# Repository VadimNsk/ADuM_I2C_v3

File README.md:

# ADuM_I2C_v3
Преобразование уровней шины I2C и двух сигналов

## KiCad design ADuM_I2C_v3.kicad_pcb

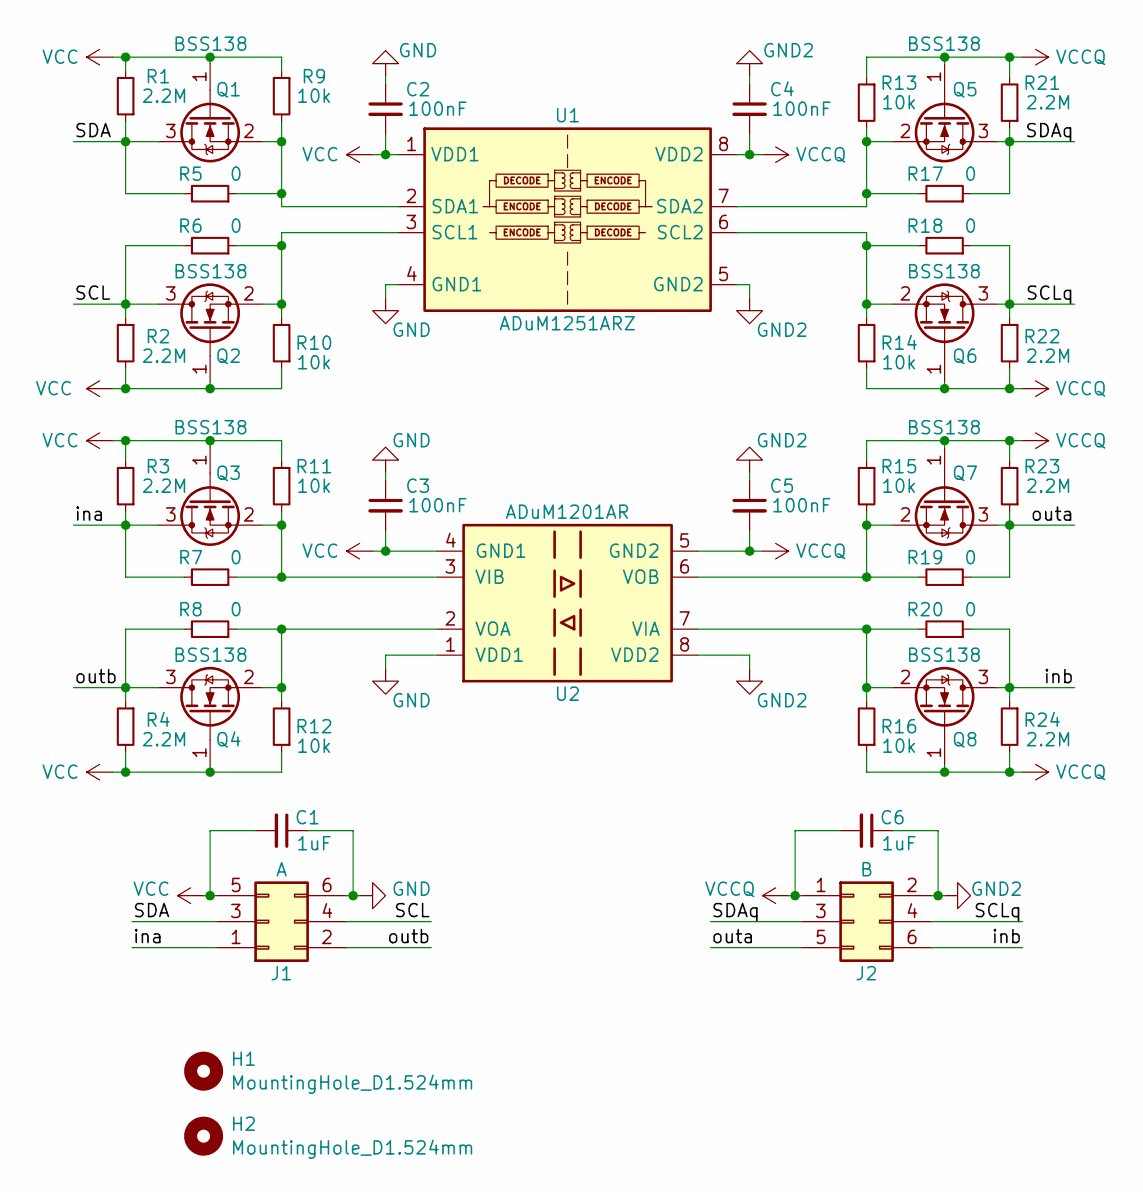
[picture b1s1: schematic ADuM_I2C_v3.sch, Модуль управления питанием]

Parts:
C1, C6: 1uF; C_0603_1608Metric
C2, C3, C4, C5: 100nF; C_0603_1608Metric
H1, H2: MountingHole_D1.524mm
J1: A; PinHeader_2x03_P1.27mm_Horizontal_short
J2: B; PinHeader_2x03_P1.27mm_Horizontal_short
Q1, Q2, Q3, Q4, Q5, Q6, Q7, Q8: BSS138; SOT-23
R1, R2, R3, R4, R21, R22, R23, R24: 2.2M; R_0603_1608Metric
R5, R6, R7, R8, R17, R18, R19, R20: 0; R_0603_1608Metric
R9, R10, R11, R12, R13, R14, R15, R16: 10k; R_0603_1608Metric
U1: ADuM1251ARZ; SOIC-8_3.9x4.9mm_P1.27mm
U2: ADuM1201AR; SOIC-8_3.9x4.9mm_P1.27mm

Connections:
/SCL: J1.4, Q2.3 (D), R2.1, R6.2
/SCLq: J2.4, Q6.3 (D), R18.1, R22.1
/SDA: J1.3, Q1.3 (D), R1.1, R5.2
/SDAq: J2.3, Q5.3 (D), R17.1, R21.1
/ina: J1.1, Q3.3 (D), R3.1, R7.2
/inb: J2.6, Q8.3 (D), R20.1, R24.1
/outa: J2.5, Q7.3 (D), R19.1, R23.1
/outb: J1.2, Q4.3 (D), R4.1, R8.2
GND: C1.1, C2.1, C3.1, J1.6, U1.4 (GND1), U2.1 (VDD1)
GND2: C4.1, C5.1, C6.1, J2.2, U1.5 (GND2), U2.8 (VDD2)
unnamed: Q1.2 (S), R5.1, R9.2, U1.2 (SDA1)
unnamed: Q2.2 (S), R6.1, R10.2, U1.3 (SCL1)
unnamed: Q3.2 (S), R7.1, R11.2, U2.3 (VIB)
unnamed: Q4.2 (S), R8.1, R12.2, U2.2 (VOA)
unnamed: Q5.2 (S), R13.2, R17.2, U1.7 (SDA2)
unnamed: Q6.2 (S), R14.2, R18.2, U1.6 (SCL2)
unnamed: Q7.2 (S), R15.2, R19.2, U2.6 (VOB)
unnamed: Q8.2 (S), R16.2, R20.2, U2.7 (VIA)
VCC: C1.2, C2.2, C3.2, J1.5, Q1.1 (G), Q2.1 (G), Q3.1 (G), Q4.1 (G), R1.2, R2.2, R3.2, R4.2, R9.1, R10.1, R11.1, R12.1, U1.1 (VDD1), U2.4 (GND1)
VCCQ: C4.2, C5.2, C6.2, J2.1, Q5.1 (G), Q6.1 (G), Q7.1 (G), Q8.1 (G), R13.1, R14.1, R15.1, R16.1, R21.2, R22.2, R23.2, R24.2, U1.8 (VDD2), U2.5 (GND2)

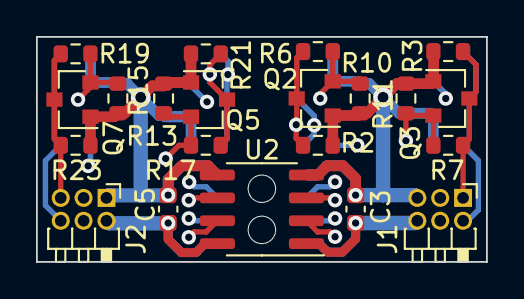
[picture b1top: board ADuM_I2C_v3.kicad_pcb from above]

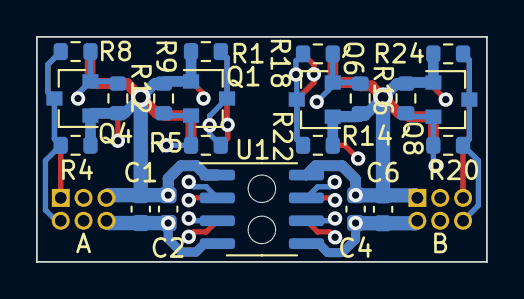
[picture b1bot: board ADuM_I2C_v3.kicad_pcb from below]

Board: 4 copper layers, 25.0 x 12.5 mm, 44 parts (21 on the bottom side), 20 nets.

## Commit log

2021-12-25 Окончена трассировка печатной платы
2022-01-01 Исправления в схеме
2022-01-18 Первый вариант генерирования гербера.
2022-01-18 Добавлен BOM файл в HTML-формате
2022-01-18 Добавлен BOM-файл в HTML-формате, гербера и файлы сверловки
2022-01-18 Сформирован перечень элементов, 3D-модель, исправлены ошибки, реализована панелизация платы.
2022-01-23 Добавил изолирующие отверстия на схему. Подправил компоненты отверстий. Удалил контуры отверстий на обеих слоях платы. Обновил гербера и 3D-модель (step-файл).
2022-02-17 Последние изменения в BOM
